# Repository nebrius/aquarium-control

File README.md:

# Aquarium Control

Automated lighting control and temperature monitoring software for an aquarium using a Raspberry Pi. Lighting can be run on a schedule, configurable by the user, that can change lights at a set time, or based on a solar event such as sunrise and sunset. This systems makes use of several services from [Azure](https://azure.microsoft.com) to handle and store aquarium data.

Note: figuring out how to connect the Pi to the lighting hardware is left as an exercise for the reader since there are so many different lighting systems out there.

Here's some photos of the system "in production" on my aquarium at home:

# License

All schematics, layouts, software, and other documentation for aquarium-control is released under the General Public License.

Copyright (C) 2013-2017 Bryan Hughes <bryan@nebri.us>

Aquarium Control is free software: you can redistribute it and/or modify
it under the terms of the GNU General Public License as published by
the Free Software Foundation, either version 3 of the License, or
(at your option) any later version.

Aquarium Control is distributed in the hope that it will be useful,
but WITHOUT ANY WARRANTY; without even the implied warranty of
MERCHANTABILITY or FITNESS FOR A PARTICULAR PURPOSE.  See the
GNU General Public License for more details.

You should have received a copy of the GNU General Public License
along with Aquarium Control.  If not, see <http://www.gnu.org/licenses/>.

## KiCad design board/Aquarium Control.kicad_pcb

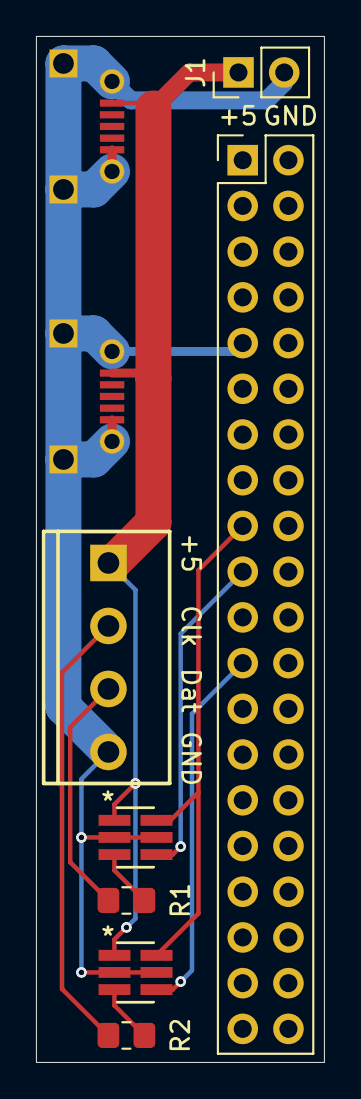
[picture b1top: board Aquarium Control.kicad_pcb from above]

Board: 2 copper layers, 16.0 x 57.0 mm, 9 parts (0 on the bottom side), 9 nets.

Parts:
J1: Conn_01x02_Pin; PinHeader_1x02_P2.54mm_Vertical
J2: CONN_04SCREW; SCREWTERMINAL-3.5MM-4
J3: Raspberry_Pi_2_3; PinHeader_2x20_P2.54mm_Vertical
R1, R2: 68; R_0805_2012Metric_Pad1.20x1.40mm_HandSolder
U1, U2: 10118194-MICRO-USB
U3, U4: SN74LVC1T45DBVRDBV6-M; DBV6-M

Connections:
+3.3V: J3.1 (3V3), J3.17 (3V3), U3.6 (VCCB), U4.6 (VCCB)
+5V: J1.1, J2.1, U1.1 (5V), U2.1 (5V), U3.1 (VCCA), U4.1 (VCCA)
GND: J1.2, J2.4, J3.6 (GND), J3.9 (GND), J3.14 (GND), J3.20 (GND), J3.25 (GND), J3.30 (GND), J3.34 (GND), J3.39 (GND), U1.5 (GND$1), U1.M1 (GND$2), U1.M2 (GND$3), U1.M3 (GND$4), U1.M4 (GND$5), U2.5 (GND$1), U2.M1 (GND$2), U2.M2 (GND$3), U2.M3 (GND$4), U2.M4 (GND$5), U3.2 (GND), U3.5 (DIR), U4.2 (GND), U4.5 (DIR)
unnamed: J2.2, R2.2
unnamed: J2.3, R1.2
unnamed: J3.19 (MOSI0/GPIO10), U3.4 (B)
unnamed: J3.23 (SCLK0/GPIO11), U4.4 (B)
unnamed: R1.1, U3.3 (A)
unnamed: R2.1, U4.3 (A)

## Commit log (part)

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2013-05-08 Finished the first draft of the board
2013-05-09 Revert "Created first stab at the layout"
    This reverts commit 80594b7f105a9c1f06d945b55b714ba1cb95abe1.
2013-05-10 Upgraded to a newer version of kicad
2013-05-10 Finished setting footprints
2013-05-11 Finished with most of the power traces
2013-05-12 Tweaked some text layouts
2013-05-13 Fleshed out index.js
2013-05-20 Wired up logging
2013-05-22 Fleshed out the template layout
2013-05-24 Finished laying out controls
2013-05-24 Tweaked the mobile layout cutoff point
2013-05-28 Fleshed out power delivery
2013-06-02 Wired up all of the config controls
2013-06-09 Removed the old layout and imported the new footprints
2013-06-09 Updated the schematic with the new footprint
2013-09-01 Created a "driver" to control the GPIO connected to the interface board
2013-09-09 Fleshed out the scheduler to work on UTC/non-localized systems like the raspberry pi
2013-11-29 Set up base configuration and created the first model
2013-12-03 Added logging to configuration
2013-12-03 Fleshed out some navbar issues
2014-02-13 Implemented the basics of the new UI
2014-02-19 Updated the server to handle the new data format
2014-02-19 Added file capping
2014-03-24 Updated the UI to work completely in UTC
2014-05-13 Removed the python driver and instead am now setting the GPIO directly
2015-07-30 I'll get it eventually
2015-07-30 Shortened the relay delay
2015-08-03 Removed extra debugging line
2015-08-05 Added more logging
2015-08-23 Set up the basic app structure
2015-08-24 Wired up override states
2015-08-24 Fleshed out program entries UI
2015-08-25 Wired up some of the edit dialog
2015-08-27 Added a logger and some license stuff
2015-08-27 Added logging to the server
2015-08-28 Worked around a (bug?) in suncalc
2015-08-31 Fixed some bugs, initial test runs
2015-09-01 Added a readme
2017-09-19 Created API system
2017-09-20 RPi now connects to IoT Hub
2017-09-20 Wired up hardware
2017-09-21 Rewrote ingester to send messages (preping for refactor)
2017-09-21 Cleaned up update rate mechanism
2017-09-25 First steps in new board
2017-09-26 Finished power supply design (hopefully)
2017-09-26 Stubbed out API
2017-09-27 Implemented DB connection code
2017-09-27 Removed old ingester code
2017-09-28 Wired up temperature to express endpoint
2017-10-03 First stab at integrating Facebook login
2017-10-07 Code cleanup
2017-10-17 Set up pug views
2017-10-20 Wired up the state endpoint
2017-10-24 Fixed an ordering bug
2017-10-26 Configuration support works in the controller and server
2017-10-26 Fleshed out schedule entries
2017-10-27 Finished configuration in the client
2017-10-31 Cleaned up auth a bit
2017-10-31 Updated the controller build to include missing common files
2017-11-24 Swapped out components to use new centralized parts repo
2018-01-04 Updated the MQTT version to bring in a security fix
2018-01-22 Reworked the server to not use stream analytics
2018-03-29 Updated to include a server ping and use the abstracted facebook auth
2018-03-29 Properly fixed the bug
2019-04-28 Partially updated the server to new dep versions
2019-04-28 Something was updated in the controller *shrug*
2019-04-29 Created record cleaning form
2019-04-29 Wired up saving the cleaning record
2019-05-03 First stab at updating to new event-hubs code
2019-05-06 Created client infrastructure for testing
2019-05-06 Theoretically implemented server support for testing
2019-06-17 First draft of rewrite
2019-06-22 Finished porting the server part to all local
2019-06-25 Reworked temperature sensing so it doesn't throw an exception when sensors are missing
2019-06-26 Cleaned up some stuff
2019-07-27 Fixed table structure
2019-12-22 Bump lodash from 4.17.11 to 4.17.15 in /server
    Bumps [lodash](https://github.com/lodash/lodash) from 4.17.11 to 4.17.15.
    - [Release notes](https://github.com/lodash/lodash/releases)
    - [Commits](https://github.com/lodash/lodash/compare/4.17.11...4.17.15)
2019-12-26 Fixed a bug with updating temperatures
2020-07-15 Bump lodash from 4.17.11 to 4.17.19 in /client
    Bumps [lodash](https://github.com/lodash/lodash) from 4.17.11 to 4.17.19.
    - [Release notes](https://github.com/lodash/lodash/releases)
    - [Commits](https://github.com/lodash/lodash/compare/4.17.11...4.17.19)
2020-12-11 Bump ini from 1.3.5 to 1.3.7 in /server
    Bumps [ini](https://github.com/isaacs/ini) from 1.3.5 to 1.3.7.
    - [Release notes](https://github.com/isaacs/ini/releases)
    - [Commits](https://github.com/isaacs/ini/compare/v1.3.5...v1.3.7)
2021-03-08 Bump elliptic from 6.4.1 to 6.5.4 in /client
    Bumps [elliptic](https://github.com/indutny/elliptic) from 6.4.1 to 6.5.4.
    - [Release notes](https://github.com/indutny/elliptic/releases)
    - [Commits](https://github.com/indutny/elliptic/compare/v6.4.1...v6.5.4)
2021-05-06 Bump lodash from 4.17.11 to 4.17.21 in /server
    Bumps [lodash](https://github.com/lodash/lodash) from 4.17.11 to 4.17.21.
    - [Release notes](https://github.com/lodash/lodash/releases)
    - [Commits](https://github.com/lodash/lodash/compare/4.17.11...4.17.21)
2021-05-10 Bump acorn from 6.1.1 to 6.4.2 in /client
    Bumps [acorn](https://github.com/acornjs/acorn) from 6.1.1 to 6.4.2.
    - [Release notes](https://github.com/acornjs/acorn/releases)
    - [Commits](https://github.com/acornjs/acorn/compare/6.1.1...6.4.2)
2021-05-12 Bump chart.js from 2.8.0 to 2.9.4 in /client
    Bumps [chart.js](https://github.com/chartjs/Chart.js) from 2.8.0 to 2.9.4.
    - [Release notes](https://github.com/chartjs/Chart.js/releases)
    - [Commits](https://github.com/chartjs/Chart.js/compare/v2.8.0...v2.9.4)
2022-02-11 Bump ajv from 6.10.0 to 6.12.6 in /client
    Bumps [ajv](https://github.com/ajv-validator/ajv) from 6.10.0 to 6.12.6.
    - [Release notes](https://github.com/ajv-validator/ajv/releases)
    - [Commits](https://github.com/ajv-validator/ajv/compare/v6.10.0...v6.12.6)
    ---
    updated-dependencies:
    - dependency-name: ajv
2022-02-11 Bump tar from 4.4.13 to 4.4.19 in /server
    Bumps [tar](https://github.com/npm/node-tar) from 4.4.13 to 4.4.19.
    - [Release notes](https://github.com/npm/node-tar/releases)
    - [Changelog](https://github.com/npm/node-tar/blob/main/CHANGELOG.md)
    - [Commits](https://github.com/npm/node-tar/compare/v4.4.13...v4.4.19)
    ---
    updated-dependencies:
2022-04-08 Bump moment from 2.24.0 to 2.29.2 in /client
    Bumps [moment](https://github.com/moment/moment) from 2.24.0 to 2.29.2.
    - [Release notes](https://github.com/moment/moment/releases)
    - [Changelog](https://github.com/moment/moment/blob/develop/CHANGELOG.md)
    - [Commits](https://github.com/moment/moment/compare/2.24.0...2.29.2)
    ---
    updated-dependencies:
2022-07-06 Bump moment from 2.24.0 to 2.29.4 in /server
    Bumps [moment](https://github.com/moment/moment) from 2.24.0 to 2.29.4.
    - [Release notes](https://github.com/moment/moment/releases)
    - [Changelog](https://github.com/moment/moment/blob/develop/CHANGELOG.md)
    - [Commits](https://github.com/moment/moment/compare/2.24.0...2.29.4)
    ---
    updated-dependencies:
2022-08-30 Bump moment-timezone from 0.5.25 to 0.5.35 in /client
    Bumps [moment-timezone](https://github.com/moment/moment-timezone) from 0.5.25 to 0.5.35.
    - [Release notes](https://github.com/moment/moment-timezone/releases)
    - [Changelog](https://github.com/moment/moment-timezone/blob/develop/changelog.md)
    - [Commits](https://github.com/moment/moment-timezone/compare/0.5.25...0.5.35)
    ---
    updated-dependencies:
2022-12-07 Bump qs from 6.5.2 to 6.5.3 in /server
    Bumps [qs](https://github.com/ljharb/qs) from 6.5.2 to 6.5.3.
    - [Release notes](https://github.com/ljharb/qs/releases)
    - [Changelog](https://github.com/ljharb/qs/blob/main/CHANGELOG.md)
    - [Commits](https://github.com/ljharb/qs/compare/v6.5.2...v6.5.3)
    ---
    updated-dependencies:
2023-01-07 Bump json5 from 1.0.1 to 1.0.2 in /client
    Bumps [json5](https://github.com/json5/json5) from 1.0.1 to 1.0.2.
    - [Release notes](https://github.com/json5/json5/releases)
    - [Changelog](https://github.com/json5/json5/blob/main/CHANGELOG.md)
    - [Commits](https://github.com/json5/json5/compare/v1.0.1...v1.0.2)
    ---
    updated-dependencies:
2025-11-17 Moved old code into backup folder
2025-11-17 Implemented tabs
2025-11-17 Finished lights visuals
2025-11-17 Set up basic backend
2025-11-17 Wired Lights UI to the backend
2025-11-18 Added board schematic
2025-11-18 Split types into shared package
2025-11-19 Stubbed server
2025-11-19 Brought in common prettier config
2025-11-19 Added color editing
2025-11-20 First draft of working scheduler
2025-11-21 Switched to web sockets for color
2025-11-22 Cleaned up dependencies
2025-11-27 Converted colors to be arbitrary
2025-11-29 Added ability to delete colors
2025-11-29 Wired up override colors to list of colors
2025-12-01 Fixed color picker
2025-12-02 Added color select to lights
2025-12-02 Made cleaning page scrollable
2025-12-03 Better algorithm to avoid green
2025-12-05 Added LED driver
2025-12-06 Checked in prod artifacts
2025-12-06 Server from server
2025-12-12 Bump next from 16.0.9 to 16.0.10 in /client
    Bumps [next](https://github.com/vercel/next.js) from 16.0.9 to 16.0.10.
    - [Release notes](https://github.com/vercel/next.js/releases)
    - [Changelog](https://github.com/vercel/next.js/blob/canary/release.js)
    - [Commits](https://github.com/vercel/next.js/compare/v16.0.9...v16.0.10)
    ---
    updated-dependencies:
2026-02-03 Bump fastify from 5.6.2 to 5.7.3 in /server
    Bumps [fastify](https://github.com/fastify/fastify) from 5.6.2 to 5.7.3.
    - [Release notes](https://github.com/fastify/fastify/releases)
    - [Commits](https://github.com/fastify/fastify/compare/v5.6.2...v5.7.3)
    ---
    updated-dependencies:
    - dependency-name: fastify
2026-03-19 Bump next from 16.1.5 to 16.1.7 in /client
    Bumps [next](https://github.com/vercel/next.js) from 16.1.5 to 16.1.7.
    - [Release notes](https://github.com/vercel/next.js/releases)
    - [Changelog](https://github.com/vercel/next.js/blob/canary/release.js)
    - [Commits](https://github.com/vercel/next.js/compare/v16.1.5...v16.1.7)
    ---
    updated-dependencies:
2026-03-21 Dep upgrades
2026-04-10 Bump next from 16.2.1 to 16.2.3
    Bumps [next](https://github.com/vercel/next.js) from 16.2.1 to 16.2.3.
    - [Release notes](https://github.com/vercel/next.js/releases)
    - [Changelog](https://github.com/vercel/next.js/blob/canary/release.js)
    - [Commits](https://github.com/vercel/next.js/compare/v16.2.1...v16.2.3)
    ---
    updated-dependencies:
2026-05-16 Upgraded to the production version of import integrity
2026-05-23 Bump qs from 6.15.1 to 6.15.2
    Bumps [qs](https://github.com/ljharb/qs) from 6.15.1 to 6.15.2.
    - [Changelog](https://github.com/ljharb/qs/blob/main/CHANGELOG.md)
    - [Commits](https://github.com/ljharb/qs/compare/v6.15.1...v6.15.2)
    ---
    updated-dependencies:
    - dependency-name: qs

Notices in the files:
board/Aquarium Control.kicad_pcb:
Copyright Bryan Hughes
